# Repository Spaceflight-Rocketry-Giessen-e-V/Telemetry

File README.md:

# ASCENT Rocket Telemetry System

|</p> | </p></p>|
|---|---|
|<p align="center">[The Onboard System](/onboard/)</p>|<p align="center">[The Groundstation System](/groundstation/)</p>|

---

## Overview

The ASCENT telemetry system is a part of the ASCENT flight computer, which is being developed by the student rocketry club [Spaceflight Rocketry Gießen e.V.](https://sprog-ev.de/en/) for the PIPE and ARCHER experimental rockets.
This dual-frequency 169/869-MHz telemetry system based on Radiocrafts RC232 radio modules allows bidirectional data exchange between rockets and groundstations with a range of more than 10 km.
The design can easily be adapted for uses outside of rocketry like Smart Home or RC.

## Basic Functionality

- Receiving flight and telemetry data from the rocket
- Sending radio commands to the rocket
- Displaying live data on a serial monitor or an UI

## Actual Performance

In January 2026, we performed our first long range test over a distance of 2 km. Despite poor weather conditions and objects inside the first Fresnel zone, the received signal strength was on par with the theoretical maximum without any unaccounted losses. This test ruled out major design flaws and was confirmed by additional medium range tests.

In April 2026, the system was successfully tested on the PIPE 2 rocket to an altitude of 350 m and experienced no link issues during the whole flight.

---

## Repository Contents

This repository contains all files necessary to reproduce the telemetry system, including hardware, firmware, software, and documentation.

### 1. Electronics Hardware

The telemetry system utilizes separate [onboard](/onboard/pcb/) and [groundstation](/groundstation/pcb/) electronics.
The groundstation uses a modular approach with a [motherboard](/groundstation/pcb/Motherboard/) to which up to four [daughterboards](/groundstation/pcb/Daughterboard/) with radio modules can be connected.

The repository includes for each system the KiCad design files including custom component schematic, footprint, and 3D model libraries, the PDF schematic, the Gerber production files, the bill of material (BOM) and an interactive BOM (iBOM). 
Renderings, images, and 3D models of the electronics are also included.

The [onboard mounting structure](/onboard/mounting%20structure/), the [motherboard and daughterboard casings](/groundstation/casing/) are included separately.

### 2. Antenna Hardware

So far, this repository includes the [design files](/groundstation/antenna/helical/) and [assembly instructions](/docs/helical_antenna_assembly_manual.md) for our helical 869 MHz groundstation antenna.

We also do our own FDTD-simulations which can be found [here](groundstation/antenna/helical/Simulation/Helical_Antenna.m).

Currently, we are developing an 869 MHz QFH antenna.

### 3. Firmware

- [Onboard Firmware](/onboard/firmware/)
- [Groundstation Firmware](/groundstation/firmware/) 
- [Radiocrafts RC17xHP-RC232 Library](/libraries/Radiocrafts_RC17xxHP_RC232/)
- [Dynamic Package Codec (Encoding/Decoding) Library](/libraries/DynamicPacketCodec/)
- [Firmware API Reference](https://spaceflight-rocketry-giessen-e-v.github.io/Telemetry/)

### 4. Groundstation UI Software

[Python-based software](/groundstation/gui/) to display live telemetry data on a modern, minimalistic interface with the ability to store flight data and send radio commands. 

Widgets include a GNSS map view, a height plot over time, an acceleration plot over time, a battery voltage indicator with visual warnings, a connection quality indicator with visual warnings, and a status event indicator.

### 5. Documentation

- [Design Overview](/docs/design_overview.md)
- [User Manual](/docs/user_manual.md) and [Operations Cheatsheet](/docs/operations_cheatsheet.md)
- Documentation of the [Packet Structure](/docs/packet_structure.md) and the [Linkbudget Calculation](/docs/linkbudget.ipynb)
- [And more...](/docs/)

---

## Legal Notice

Please note that radio systems may be subject to local regulations. Ensure that any testing or deployment of these systems complies with national and regional laws regarding RF transmission. Spaceflight Rocketry Giessen e.V. and the individual project contributors are not responsible for misuse or regulatory violations.  

## License

This source describes Open Hardware and is licensed under the CERN-OHL-S v2.<br>
You may redistribute and modify this source and make products using it under the terms of the [CERN-OHL-S v2 or any later version](LICENSE).<br>
This source is distributed without any express or implied warranty, including of merchantability, satifactory quality and fitness for a particular purpose. Please see the CERN-OHL-S v2 for applicable conditions.<br>
Source location: https://github.com/Spaceflight-Rocketry-Giessen-e-V/Telemetry<br>
As per CERN-OHL-S v2 section 4, should you produce hardware based on this source, you must where practicable maintain the Source Location in its documentation or license information.<br><br>
Copyright 2026 Spaceflight Rocketry Giessen e.V. \<elektronik@sprog-ev.de\>

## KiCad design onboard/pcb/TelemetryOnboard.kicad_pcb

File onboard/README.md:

# The Onboard System

- [Electronics Hardware](/onboard/pcb/)
    - [KiCad Design Files](/onboard/pcb/)
    - [PDF Schematic](/onboard/pcb/TelemetryOnboard_Schematic.pdf)
    - [Interactive Schematic / iBOM](/onboard/pcb/TelemetryOnboard_iBOM.html)
    - [BOM](/onboard/pcb/TelemetryOnboard_BOM.csv)
    - [Gerber Files](/onboard/pcb/Production%20Files/)
    - [PCB 3D Model](/onboard/pcb/TelemetryOnboard.step)
    - [PCB Images](/onboard/pcb/images/)
- [Mounting Structure](/onboard/mounting%20structure/)
- [Firmware](/onboard/firmware/)
- [869 MHz QFH Antenna](/onboard/antenna/) (not yet available)

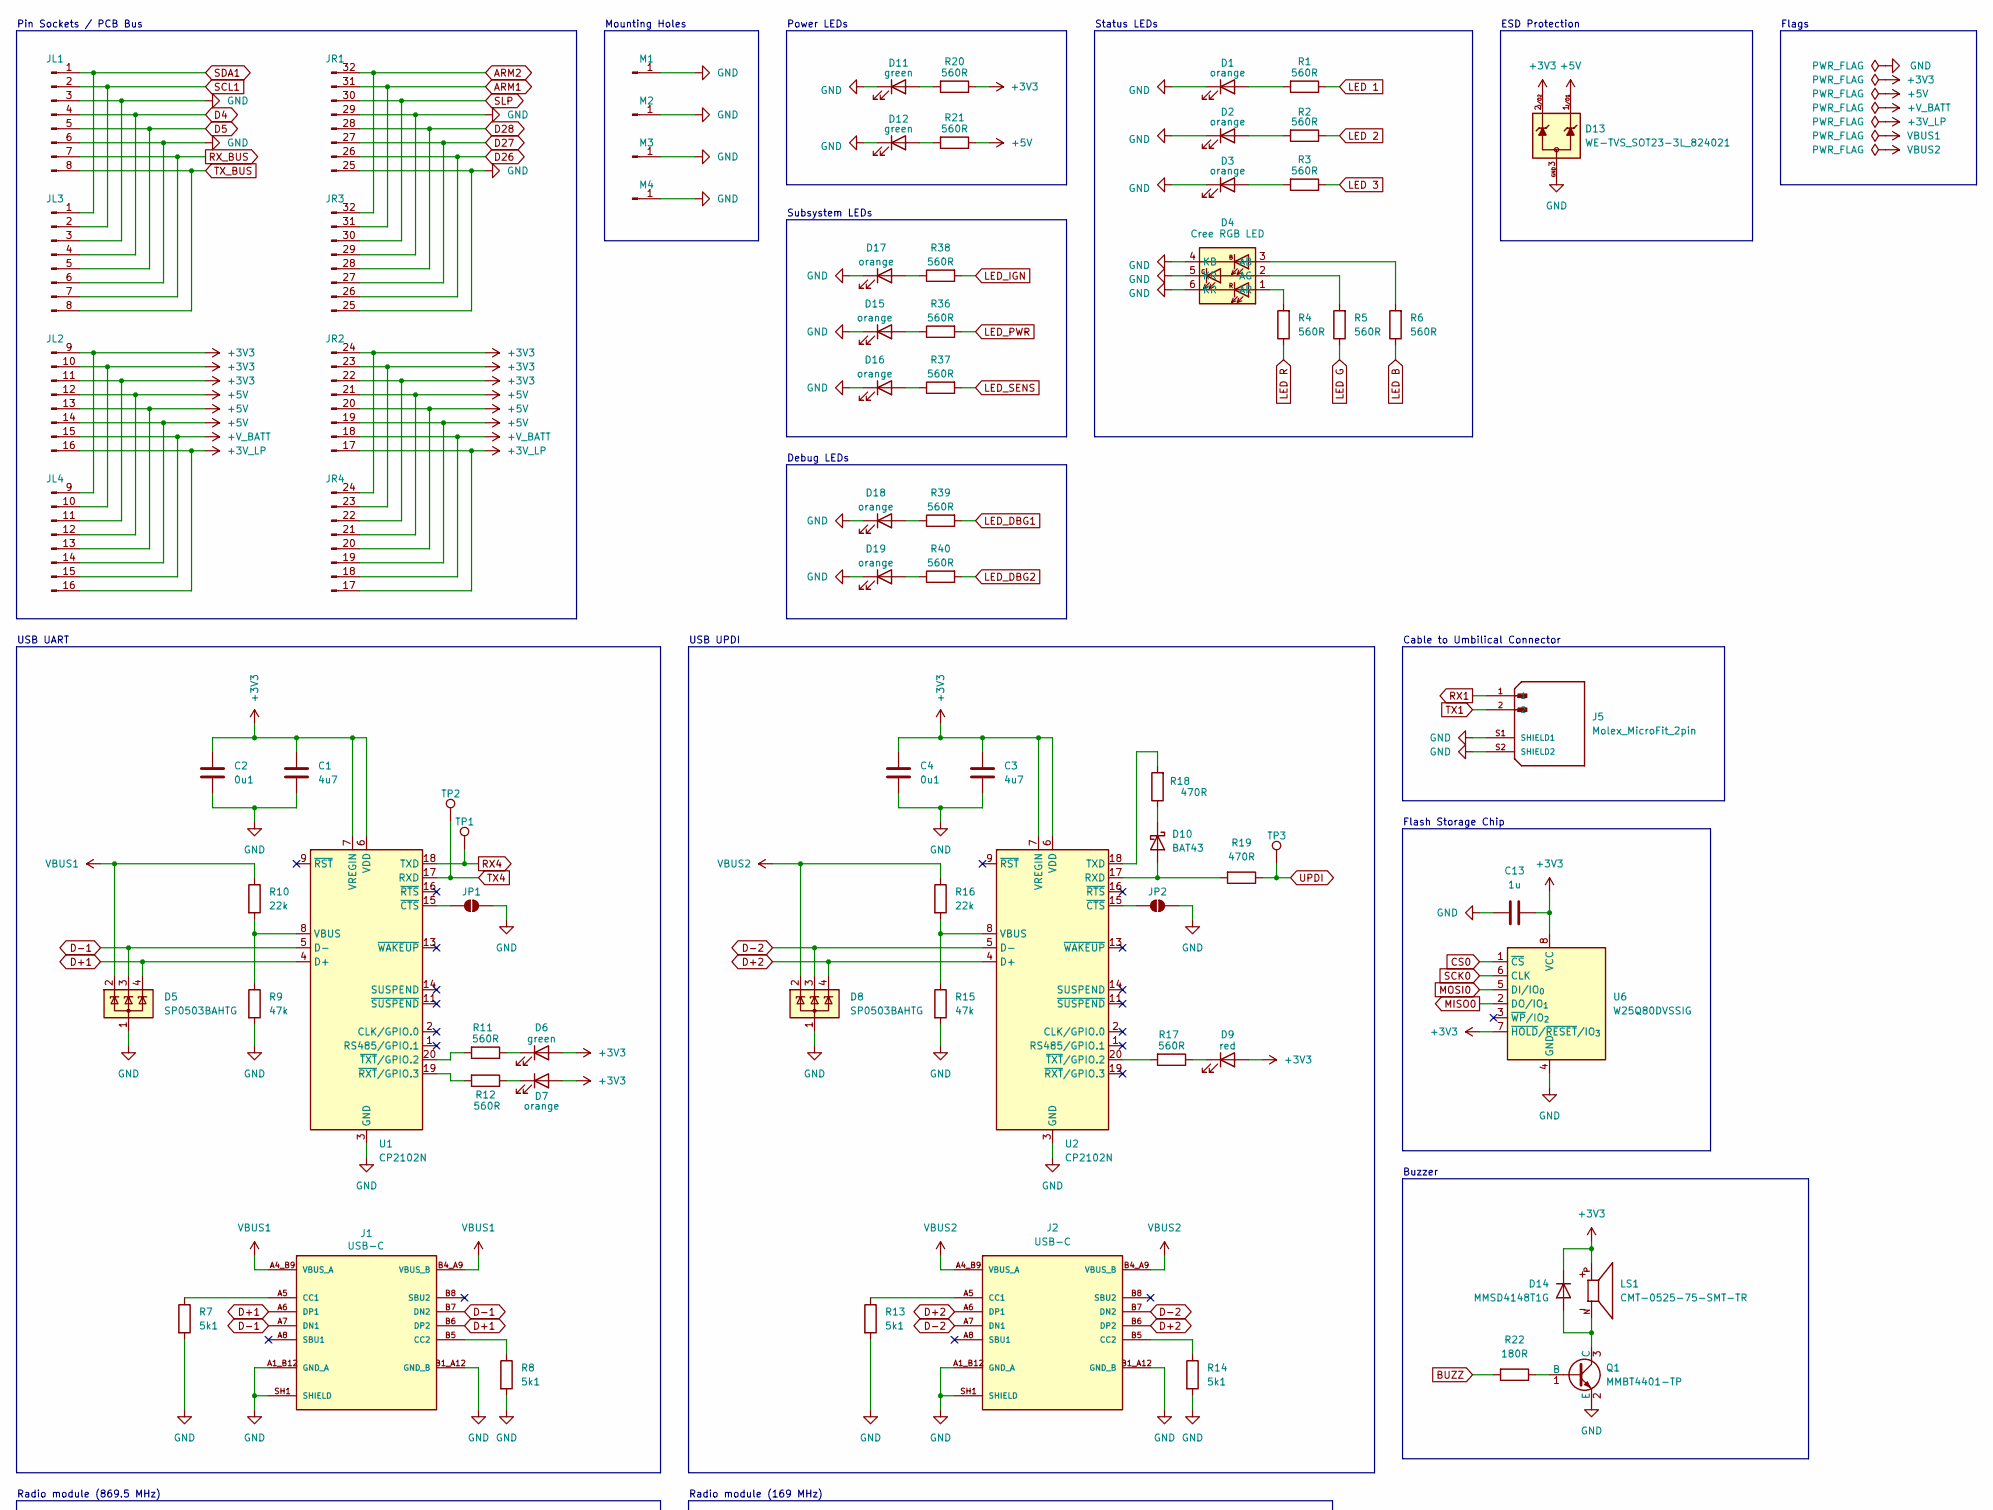
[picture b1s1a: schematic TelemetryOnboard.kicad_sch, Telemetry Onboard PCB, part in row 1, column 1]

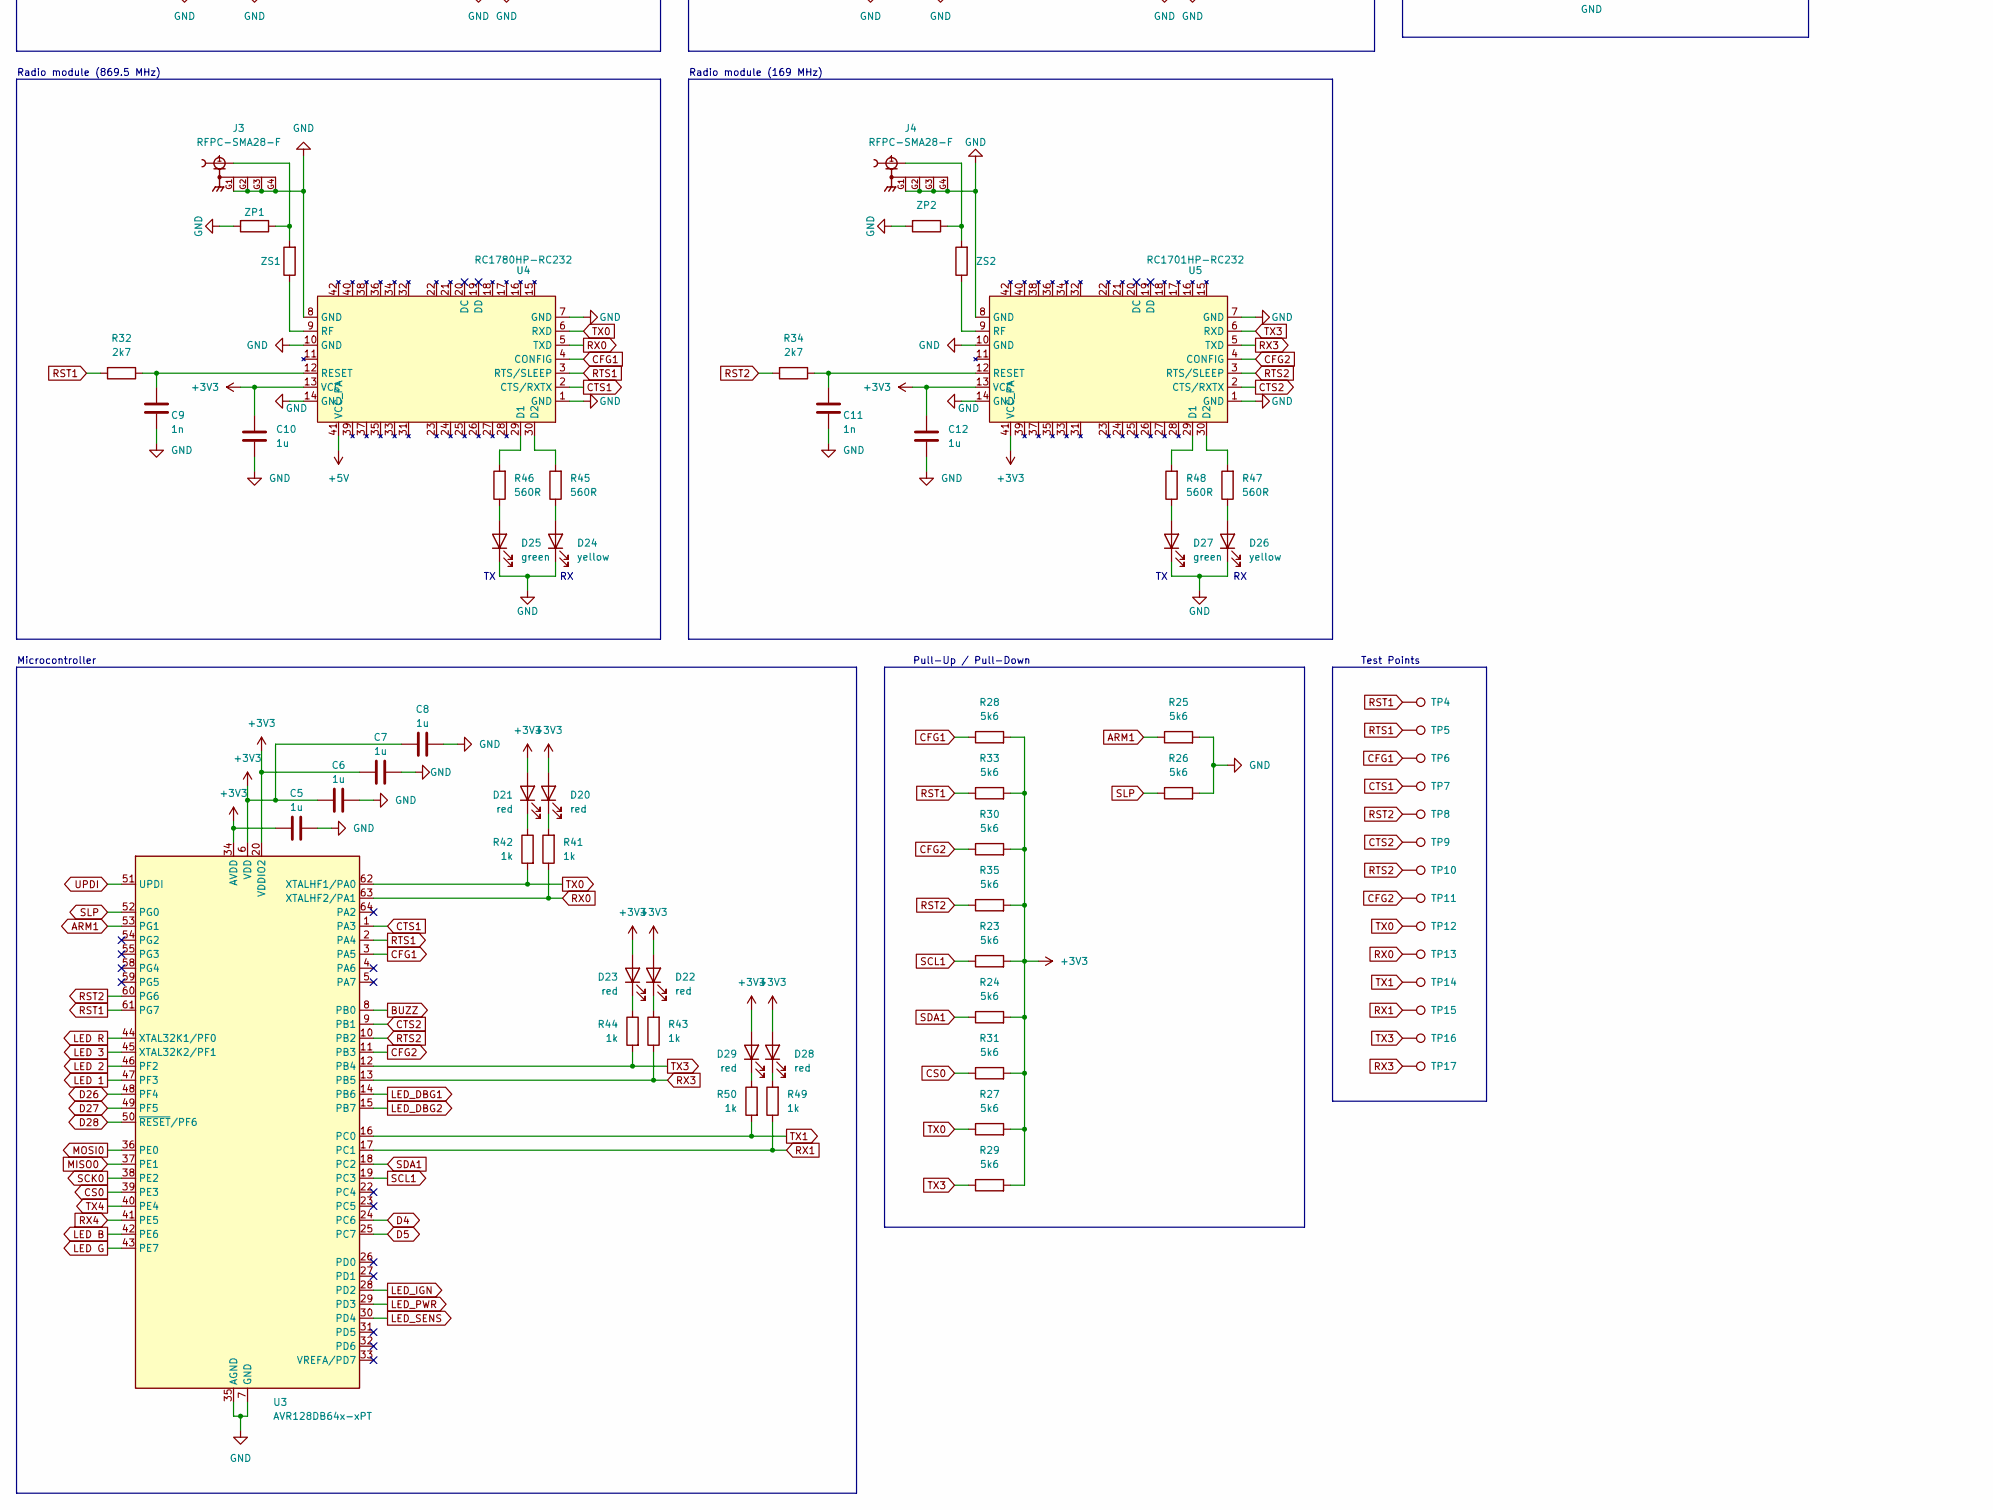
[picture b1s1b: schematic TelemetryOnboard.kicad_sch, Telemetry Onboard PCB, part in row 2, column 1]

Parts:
C1, C3: 4u7; C_0805_2012Metric_Pad1.18x1.45mm_HandSolder
C2, C4: 0u1; C_0805_2012Metric_Pad1.18x1.45mm_HandSolder
C5, C6, C7, C8, C10, C12, C13: 1u; C_0805_2012Metric_Pad1.18x1.45mm_HandSolder
C9, C11: 1n; C_0805_2012Metric_Pad1.18x1.45mm_HandSolder
D1, D2, D3, D7, D15, D16, D17, D18, D19: orange; LED_0805_2012Metric_Pad1.15x1.40mm_HandSolder
D4: Cree RGB LED; Cree_PLCC6_RGB
D5, D8: SP0503BAHTG; SOT-143
D6, D11, D12, D25, D27: green; LED_0805_2012Metric_Pad1.15x1.40mm_HandSolder
D9, D20, D21, D22, D23, D28, D29: red; LED_0805_2012Metric_Pad1.15x1.40mm_HandSolder
D10: BAT43; D_SOD-123
D13: WE-TVS_SOT23-3L_824021; SOT-23-3
D14: MMSD4148T1G; D_SOD-123
D24, D26: yellow; LED_0805_2012Metric_Pad1.15x1.40mm_HandSolder
J1, J2: USB-C; GTC_USB4216_SMD; PARTREV A; DigiKey_Part_Number 2073-USB4215-03-ACT-ND
J3, J4: RFPC-SMA28-F; SMA_Amphenol_901-144_Vertical; PARTREV 1.0; DigiKey_Part_Number 2073-RFPC-SMA28-F-ND
J5: Molex_MicroFit_2pin; Molex_MicroFit-2pos; PARTREV F3; DigiKey_Part_Number WM1870-ND
JL1: Stackable Socket 1x8; JL1
JL2: Stackable Socket 1x8; JL2
JL3: Stackable Socket 1x8; JL3
JL4: Stackable Socket 1x8; JL4
JP1, JP2: SolderJumper_2_Open; Custom_SolderJumper
JR1: Stackable Socket 1x8; JR1
JR2: Stackable Socket 1x8; JR2
JR3: Stackable Socket 1x8; JR3
JR4: Stackable Socket 1x8; JR4
LS1: CMT-0525-75-SMT-TR; SameSky_CMT-0525-75-SMT_Buzzer; PARTREV 1.0
M1, M2, M3, M4: M4 Mounting Hole; Custom_M4Hole
Q1: MMBT4401-TP; SOT-23
R1, R2, R3, R4, R5, R6, R11, R12, R17, R20, R21, R36, R37, R38, R39, R40, R45, R46, R47, R48: 560R; R_0805_2012Metric_Pad1.20x1.40mm_HandSolder
R7, R8, R13, R14: 5k1; R_0805_2012Metric_Pad1.20x1.40mm_HandSolder
R9, R15: 47k; R_0805_2012Metric_Pad1.20x1.40mm_HandSolder
R10, R16: 22k; R_0805_2012Metric_Pad1.20x1.40mm_HandSolder
R18, R19: 470R; R_0805_2012Metric_Pad1.20x1.40mm_HandSolder
R22: 180R; R_0805_2012Metric_Pad1.20x1.40mm_HandSolder
R23, R24, R25, R26, R27, R28, R29, R30, R31, R33, R35: 5k6; R_0805_2012Metric_Pad1.20x1.40mm_HandSolder
R32, R34: 2k7; R_0805_2012Metric_Pad1.20x1.40mm_HandSolder
R41, R42, R43, R44, R49, R50: 1k; R_0805_2012Metric_Pad1.20x1.40mm_HandSolder
TP1, TP2, TP3, TP4, TP5, TP6, TP7, TP8, TP9, TP10, TP11, TP12, TP13, TP14, TP15, TP16, TP17: TestPoint; Custom_SolderJumper
U1, U2: CP2102N; SiLabs_CP2102N_QFN20.step
U3: AVR128DB64x-xPT; TQFP-64_10x10mm_P0.5mm
U4: RC1780HP-RC232; Radiocrafts_RC17xxHP-RC232
U5: RC1701HP-RC232; Radiocrafts_RC17xxHP-RC232
U6: W25Q80DVSSIG; SOIC-8_5.3x5.3mm_P1.27mm
ZP1, ZP2: R_0805_2012Metric_Pad1.20x1.40mm_HandSolder
ZS1, ZS2: R_0805_2012Metric_Pad1.20x1.40mm_HandSolder

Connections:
+3V3: C1.1, C2.1, C3.1, C4.1, C5.1, C6.1, C7.2, C8.2, C10.1, C12.1, C13.2, D6.2 (A), D7.2 (A), D9.2 (A), D13.2 (K), D14.1 (K), D20.2 (A), D21.2 (A), D22.2 (A), D23.2 (A), D28.2 (A), D29.2 (A), JL2.9 (Pin_1), JL2.10 (Pin_2), JL2.11 (Pin_3), JL4.9 (Pin_1), JL4.10 (Pin_2), JL4.11 (Pin_3), JR2.22 (26), JR2.23 (Pin_2), JR2.24 (Pin_1), JR4.22 (26), JR4.23 (Pin_2), JR4.24 (Pin_1), LS1.P, R20.1, R23.2, R24.2, R27.2, R28.2, R29.2, R30.2, R31.2, R33.2, R35.2, U1.6 (VDD), U1.7 (VREGIN), U2.6 (VDD), U2.7 (VREGIN), U3.6 (VDD), U3.20 (VDDIO2), U3.34 (AVDD), U3.56 (VDD), U4.13 (VCC), U5.13 (VCC), U5.41 (VCC_PA), U6.7 (~HOLD/~RESET/IO_{3}), U6.8 (VCC)
+3V_LP: JL2.16 (Pin_8), JL4.16 (Pin_8), JR2.17 (Pin_8), JR4.17 (Pin_8)
+5V: D13.1 (K), JL2.12 (Pin_4), JL2.13 (Pin_5), JL2.14 (Pin_6), JL4.12 (Pin_4), JL4.13 (Pin_5), JL4.14 (Pin_6), JR2.19 (Pin_6), JR2.20 (Pin_5), JR2.21 (Pin_4), JR4.19 (Pin_6), JR4.20 (Pin_5), JR4.21 (Pin_4), R21.1, U4.41 (VCC_PA)
+V_BATT: JL2.15 (Pin_7), JL4.15 (Pin_7), JR2.18 (Pin_7), JR4.18 (Pin_7)
ARM1: JR1.31 (Pin_2), JR3.31 (Pin_2), R25.1, U3.53 (PG1)
ARM2: JR1.32 (Pin_1), JR3.32 (Pin_1)
BUZZ: R22.2, U3.8 (PB0)
CFG1: R28.1, TP6.1 (1_1), U3.3 (PA5), U4.4 (CONFIG)
CFG2: R30.1, TP11.1 (1_1), U3.11 (PB3), U5.4 (CONFIG)
CS0: R31.1, U3.39 (PE3), U6.1 (~CS)
CTS1: TP7.1 (1_1), U3.1 (PA3), U4.2 (CTS/RXTX)
CTS2: TP9.1 (1_1), U3.9 (PB1), U5.2 (CTS/RXTX)
D4: JL1.4, JL3.4, U3.24 (PC6)
D5: JL1.5, JL3.5, U3.25 (PC7)
D26: JR1.26 (Pin_7), JR3.26 (Pin_7), U3.48 (PF4)
D27: JR1.27 (Pin_6), JR3.27 (Pin_6), U3.49 (PF5)
D28: JR1.28 (Pin_5), JR3.28 (Pin_5), U3.50 (~RESET/PF6)
D+1: D5.4 (K), J1.A6 (DP1), J1.B6 (DP2), U1.4 (D+)
D+2: D8.4 (K), J2.A6 (DP1), J2.B6 (DP2), U2.4 (D+)
D-1: D5.3 (K), J1.A7 (DN1), J1.B7 (DN2), U1.5 (D-)
D-2: D8.3 (K), J2.A7 (DN1), J2.B7 (DN2), U2.5 (D-)
GND: C1.2, C2.2, C3.2, C4.2, C5.2, C6.2, C7.1, C8.1, C9.2, C10.2, C11.2, C12.2, C13.1, D1.1 (K), D2.1 (K), D3.1 (K), D4.4 (KB), D4.5 (KG), D4.6 (KR), D5.1 (A), D8.1 (A), D11.1 (K), D12.1 (K), D13.3 (A), D15.1 (K), D16.1 (K), D17.1 (K), D18.1 (K), D19.1 (K), D24.1 (K), D25.1 (K), D26.1 (K), D27.1 (K), J1.A1_B12 (GND_A), J1.B1_A12 (GND_B), J1.SH1 (SHIELD), J1.SH2 (SHIELD), J1.SH3 (SHIELD), J1.SH4 (SHIELD), J2.A1_B12 (GND_A), J2.B1_A12 (GND_B), J2.SH1 (SHIELD), J2.SH2 (SHIELD), J2.SH3 (SHIELD), J2.SH4 (SHIELD), J3.2 (Ext), J3.G1, J3.G2, J3.G3, J3.G4, J4.2 (Ext), J4.G1, J4.G2, J4.G3, J4.G4, J5.S1 (SHIELD), J5.S2 (SHIELD), JL1.3, JL1.6, JL3.3, JL3.6, JP1.2 (B), JP2.2 (B), JR1.25 (Pin_8), JR1.29 (Pin_4), JR3.25 (Pin_8), JR3.29 (Pin_4), M1.1 (Pin_1_1), M2.1 (Pin_1_1), M3.1 (Pin_1_1), M4.1 (Pin_1_1), Q1.2 (E), R7.2, R8.2, R9.2, R13.2, R14.2, R15.2, R25.2, R26.2, U1.3 (GND), U1.12 (GND), U1.21 (GND), U2.3 (GND), U2.12 (GND), U2.21 (GND), U3.7 (GND), U3.21 (GND), U3.35 (AGND), U3.57 (GND), U4.1 (GND), U4.7 (GND), U4.8 (GND), U4.10 (GND), U4.14 (GND), U5.1 (GND), U5.7 (GND), U5.8 (GND), U5.10 (GND), U5.14 (GND), U6.4 (GND), ZP1.2, ZP2.2
LED 1: R1.1, U3.47 (PF3)
LED 2: R2.1, U3.46 (PF2)
LED 3: R3.1, U3.45 (XTAL32K2/PF1)
LED B: R6.1, U3.42 (PE6)
LED G: R5.1, U3.43 (PE7)
LED R: R4.1, U3.44 (XTAL32K1/PF0)
LED_DBG1: R39.2, U3.14 (PB6)
LED_DBG2: R40.2, U3.15 (PB7)
LED_IGN: R38.2, U3.28 (PD2)
LED_PWR: R36.2, U3.29 (PD3)
LED_SENS: R37.2, U3.30 (PD4)
MISO0: U3.37 (PE1), U6.2 (DO/IO_{1})
MOSI0: U3.36 (PE0), U6.5 (DI/IO_{0})
unnamed: D1.2 (A), R1.2
unnamed: D2.2 (A), R2.2
unnamed: D3.2 (A), R3.2
unnamed: D4.3 (AB), R6.2
unnamed: D4.2 (AG), R5.2
unnamed: D4.1 (AR), R4.2
unnamed: D6.1 (K), R11.1
unnamed: D7.1 (K), R12.1
unnamed: D9.1 (K), R17.1
unnamed: D10.2 (A), R19.2, U2.17 (RXD)
unnamed: D10.1 (K), R18.1
unnamed: D11.2 (A), R20.2
unnamed: D12.2 (A), R21.2
unnamed: D14.2 (A), LS1.N, Q1.3 (C)
unnamed: D15.2 (A), R36.1
unnamed: D16.2 (A), R37.1
unnamed: D17.2 (A), R38.1
unnamed: D18.2 (A), R39.1
unnamed: D19.2 (A), R40.1
unnamed: D20.1 (K), R41.2
unnamed: D21.1 (K), R42.1
unnamed: D22.1 (K), R43.2
unnamed: D23.1 (K), R44.1
unnamed: D24.2 (A), R45.1
unnamed: D25.2 (A), R46.1
unnamed: D26.2 (A), R47.1
unnamed: D27.2 (A), R48.1
unnamed: D28.1 (K), R49.2
unnamed: D29.1 (K), R50.1
unnamed: J1.A5 (CC1), R7.1
unnamed: J1.B5 (CC2), R8.1
unnamed: J2.A5 (CC1), R13.1
unnamed: J2.B5 (CC2), R14.1
unnamed: J3.1 (In), ZP1.1, ZS1.2
unnamed: J4.1 (In), ZP2.1, ZS2.2
unnamed: JP1.1 (A), U1.15 (~CTS)
unnamed: JP2.1 (A), U2.15 (~CTS)
unnamed: Q1.1 (B), R22.1
unnamed: R9.1, R10.2, U1.8 (VBUS)
unnamed: R12.2, U1.19 (~RXT/GPIO.3)
unnamed: R11.2, U1.20 (~TXT/GPIO.2)
unnamed: R18.2, U2.18 (TXD)
unnamed: R15.1, R16.2, U2.8 (VBUS)
unnamed: R17.2, U2.20 (~TXT/GPIO.2)
unnamed: R46.2, U4.29 (D1)
unnamed: R45.2, U4.30 (D2)
unnamed: C9.1, R32.1, U4.12 (RESET)
unnamed: U4.9 (RF), ZS1.1
unnamed: R48.2, U5.29 (D1)
unnamed: R47.2, U5.30 (D2)
unnamed: C11.1, R34.1, U5.12 (RESET)
unnamed: U5.9 (RF), ZS2.1
RST1: R32.2, R33.1, TP4.1 (1_1), U3.61 (PG7)
RST2: R34.2, R35.1, TP8.1 (1_1), U3.60 (PG6)
RTS1: TP5.1 (1_1), U3.2 (PA4), U4.3 (RTS/SLEEP)
RTS2: TP10.1 (1_1), U3.10 (PB2), U5.3 (RTS/SLEEP)
RX0: R41.1, TP13.1 (1_1), U3.63 (XTALHF2/PA1), U4.5 (TXD)
RX1: J5.1, R49.1, TP15.1 (1_1), U3.17 (PC1)
RX3: R43.1, TP17.1 (1_1), U3.13 (PB5), U5.5 (TXD)
RX4: TP1.1 (1_1), U1.18 (TXD), U3.41 (PE5)
RX_BUS: JL1.7, JL3.7
SCK0: U3.38 (PE2), U6.6 (CLK)
SCL1: JL1.2, JL3.2, R23.1, U3.19 (PC3)
SDA1: JL1.1, JL3.1, R24.1, U3.18 (PC2)
SLP: JR1.30 (26), JR3.30 (26), R26.1, U3.52 (PG0)
TX0: R27.1, R42.2, TP12.1 (1_1), U3.62 (XTALHF1/PA0), U4.6 (RXD)
TX1: J5.2, R50.2, TP14.1 (1_1), U3.16 (PC0)
TX3: R29.1, R44.2, TP16.1 (1_1), U3.12 (PB4), U5.6 (RXD)
TX4: TP2.1 (1_1), U1.17 (RXD), U3.40 (PE4)
TX_BUS: JL1.8, JL3.8
UPDI: R19.1, TP3.1 (1_1), U3.51 (UPDI)
VBUS1: D5.2 (K), J1.A4_B9 (VBUS_A), J1.B4_A9 (VBUS_B), R10.1
VBUS2: D8.2 (K), J2.A4_B9 (VBUS_A), J2.B4_A9 (VBUS_B), R16.1

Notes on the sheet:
Subsystem LEDs
Pull-Up / Pull-Down
Pin Sockets / PCB Bus
Flash Storage Chip
Microcontroller
Radio module (169 MHz)
Flags
USB UPDI
Test Points
Buzzer
USB UART
Status LEDs
Debug LEDs
Mounting Holes
Power LEDs
ESD Protection
Radio module (869.5 MHz)
Cable to Umbilical Connector

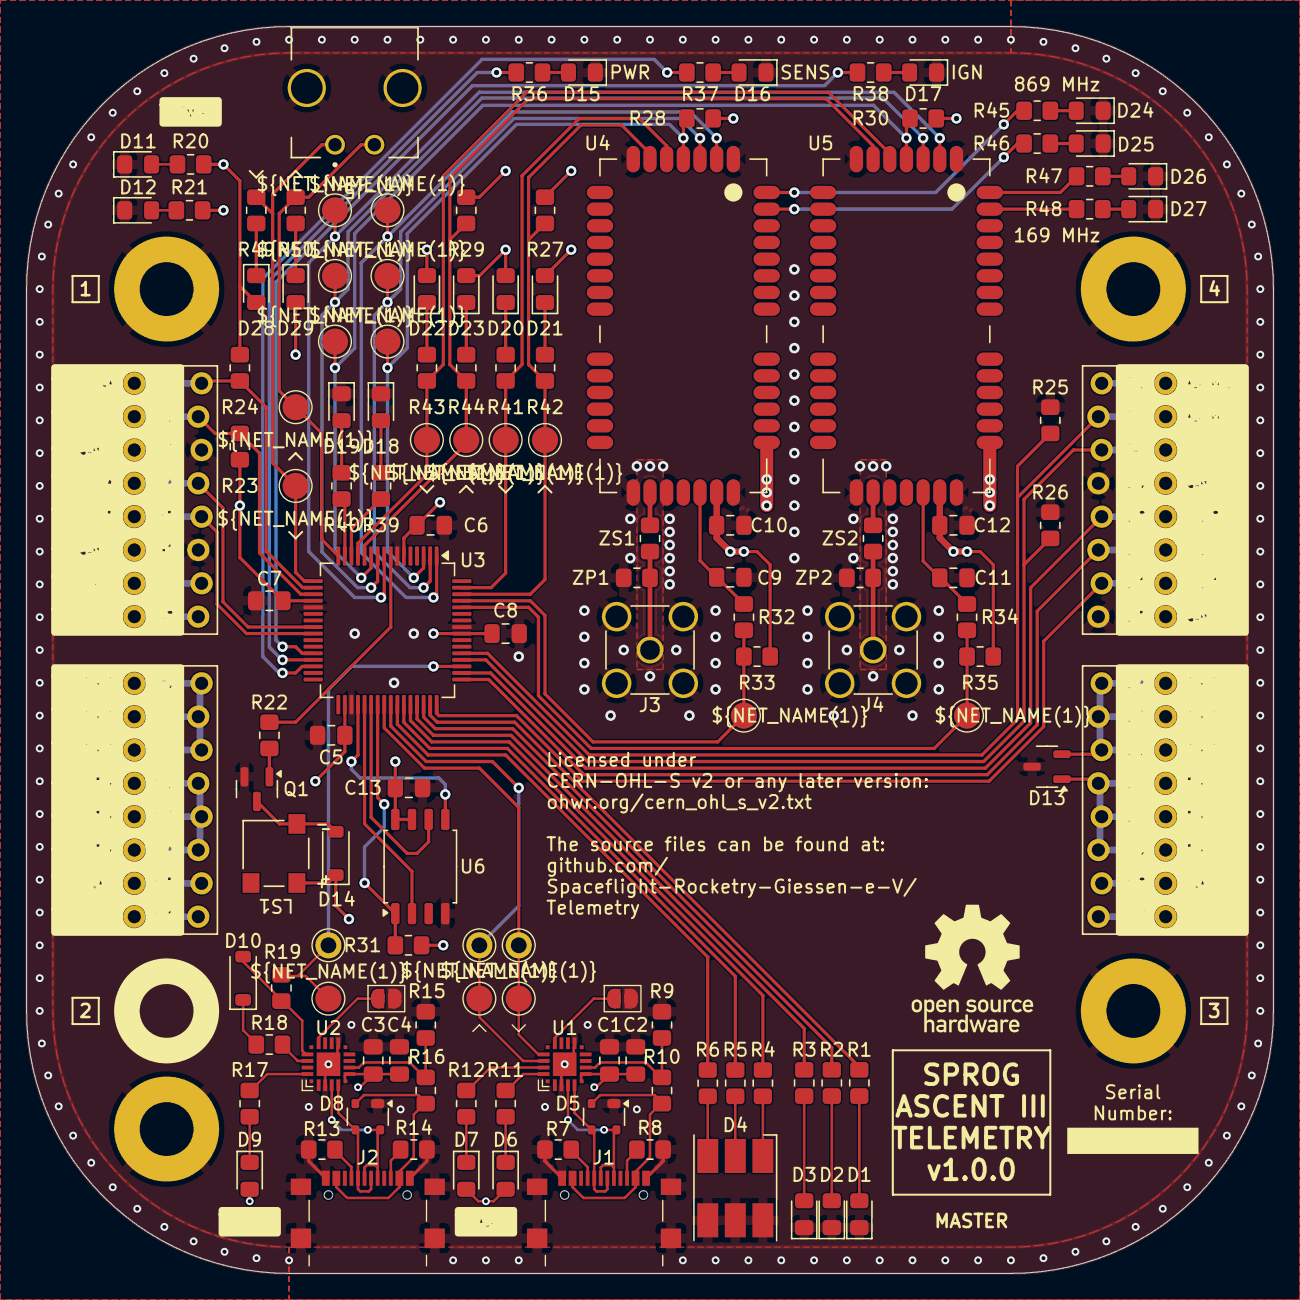
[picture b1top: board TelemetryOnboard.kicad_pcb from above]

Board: 4 copper layers, 95.0 x 95.0 mm, 140 parts (0 on the bottom side), 108 nets.

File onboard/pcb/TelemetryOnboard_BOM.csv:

"Reference","Qty","Value","Footprint","DNP","Purchase-URL"
"C1,C3","2","4u7","Capacitor_SMD:C_0805_2012Metric_Pad1.18x1.45mm_HandSolder","","https://www.digikey.de/de/products/detail/samsung-electro-me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"
"C2,C4","2","0u1","Capacitor_SMD:C_0805_2012Metric_Pad1.18x1.45mm_HandSolder","","https://www.digikey.de/de/products/detail/samsung-electro-me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"
"C5,C6,C7,C8,C10,C12,C13","7","1u","Capacitor_SMD:C_0805_2012Metric_Pad1.18x1.45mm_HandSolder","","https://www.digikey.de/de/products/detail/samsung-electro-me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"
"C9,C11","2","1n","Capacitor_SMD:C_0805_2012Metric_Pad1.18x1.45mm_HandSolder","","https://www.digikey.de/de/products/detail/samsung-electro-me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"
"D1,D2,D3,D7,D15,D16,D17,D18,D19","9","orange","LED_SMD:LED_0805_2012Metric_Pad1.15x1.40mm_HandSolder","","https://www.digikey.de/de/products/detail/liteon/LTST-C170KF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"
"D4","1","Cree RGB LED","Footprints:Cree RGB LED","","https://www.digikey.de/de/products/detail/cree-led/CLP6C-FKB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"
"D5,D8","2","SP0503BAHTG","Package_TO_SOT_SMD:SOT-143","","https://www.digikey.de/de/products/detail/littelfuse-inc/SP0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"
"D6,D11,D12,D25,D27","5","green","LED_SMD:LED_0805_2012Metric_Pad1.15x1.40mm_HandSolder","","https://www.digikey.de/de/products/detail/liteon/LTST-C171KG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"
"D9,D20,D21,D22,D23,D28,D29","7","red","LED_SMD:LED_0805_2012Metric_Pad1.15x1.40mm_HandSolder","","https://www.digikey.de/de/products/detail/liteon/LTST-C171KR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"
"D10","1","BAT43","Diode_SMD:D_SOD-123","","https://www.digikey.de/de/products/detail/mcc-micro-commerci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"
"D13","1","WE-TVS_SOT23-3L_824021","Package_TO_SOT_SMD:SOT-23-3","","https://www.digikey.de/de/products/detail/w%C3%BCrth-elektro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"
"D14","1","MMSD4148T1G","Diode_SMD:D_SOD-123","","https://www.digikey.de/de/products/detail/onsemi/MMSD4148T1G/919705"
"D24,D26","2","yellow","LED_SMD:LED_0805_2012Metric_Pad1.15x1.40mm_HandSolder","","https://www.digikey.de/de/products/detail/liteon/LTST-C170KS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"
"J1,J2","2","USB-C","Footprints:GCT_USB4216-03-A_REVA","","https://www.digikey.de/de/products/detail/gct/USB4216-03-A/26598207"
"J3,J4","2","RFPC-SMA28-F","Footprints:RFPC-SMA28-F","","https://www.digikey.de/de/products/detail/gct/RFPC-SMA28-F/2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"
"J5","1","Molex_MicroFit_2pin","Footprints:Molex_MicroFit_2pin","","https://www.digikey.de/de/products/detail/molex/0436500203/268999"
"JL1,JL2,JL3,JL4","4","Stackable Socket 1x8","Footprints:JL1,Footprints:JL2,Footprints:JL3,Footprints:JL4","","https://www.digikey.de/de/products/detail/samtec-inc/ESQ-108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,~"
"JR1,JR2,JR3,JR4","4","Stackable Socket 1x8","Footprints:JR1,Footprints:JR2,Footprints:JR3,Footprints:JR4","","https://www.digikey.de/de/products/detail/samtec-inc/ESQ-108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,~"
"LS1","1","CMT-0525-75-SMT-TR","Footprints:Buzzer XDCR_CMT-0525-75-SMT-TR","","https://www.digikey.de/de/products/detail/same-sky-formerly-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"
"M1,M2,M3,M4","4","M4 Mounting Hole","Footprints:M4 Mounting Hole","","~"
"Q1","1","MMBT4401-TP","Package_TO_SOT_SMD:SOT-23","","https://www.digikey.de/de/products/detail/mcc-micro-commerci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"
"R1,R2,R3,R4,R5,R6,R11,R12,R17,R20,R21,R36,R37,R38,R39,R40,R45,R46,R47,R48","20","560R","Resistor_SMD:R_0805_2012Metric_Pad1.20x1.40mm_HandSolder","","https://www.digikey.de/de/products/detail/stackpole-electron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"
"R7,R8,R13,R14","4","5k1","Resistor_SMD:R_0805_2012Metric_Pad1.20x1.40mm_HandSolder","","https://www.digikey.de/de/products/detail/stackpole-electron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"
"R9,R15","2","47k","Resistor_SMD:R_0805_2012Metric_Pad1.20x1.40mm_HandSolder","","https://www.digikey.de/de/products/detail/stackpole-electron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"
"R10,R16","2","22k","Resistor_SMD:R_0805_2012Metric_Pad1.20x1.40mm_HandSolder","","https://www.digikey.de/de/products/detail/stackpole-electron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"
"R18,R19","2","470R","Resistor_SMD:R_0805_2012Metric_Pad1.20x1.40mm_HandSolder","","https://www.digikey.de/de/products/detail/stackpole-electron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"
"R22","1","180R","Resistor_SMD:R_0805_2012Metric_Pad1.20x1.40mm_HandSolder","","https://www.digikey.de/de/products/detail/stackpole-electron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"
"R23,R24,R25,R26,R27,R28,R29,R30,R31,R33,R35","11","5k6","Resistor_SMD:R_0805_2012Metric_Pad1.20x1.40mm_HandSolder","","https://www.digikey.de/de/products/detail/stackpole-electron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"
"R32,R34","2","2k7","Resistor_SMD:R_0805_2012Metric_Pad1.20x1.40mm_HandSolder","","https://www.digikey.de/de/products/detail/stackpole-electron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"
"R41,R42,R43,R44,R49,R50","6","1k","Resistor_SMD:R_0805_2012Metric_Pad1.20x1.40mm_HandSolder","","https://www.digikey.de/de/products/detail/stackpole-electron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"
"TP1,TP2,TP3,TP4,TP5,TP6,TP7,TP8,TP9,TP10,TP11,TP12,TP13,TP14,TP15,TP16,TP17","17","TestPoint","Footprints:Test Point","","~"
"U1,U2","2","CP2102N","Footprints:QFN20_CP2102N_SIL","","https://www.digikey.de/de/products/detail/silicon-labs/CP210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"
"U3","1","AVR128DB64x-xPT","Package_QFP:TQFP-64_10x10mm_P0.5mm","","https://www.digikey.de/de/products/detail/microchip-technolo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"
"U4","1","RC1780HP-RC232","Footprints:Radiocrafts RC1780HP-RC232","","https://www.digikey.de/de/products/detail/radiocrafts-as/RC1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"
"U5","1","RC1701HP-RC232","Footprints:Radiocrafts RC1780HP-RC232","","https://www.digikey.de/de/products/detail/radiocrafts-as/RC1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"
"U6","1","W25Q80DVSSIG","Package_SO:SOIC-8_5.3x5.3mm_P1.27mm","","https://www.digikey.de/de/products/detail/winbond-electronic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"
"ZP1,ZP2","2","~","Resistor_SMD:R_0805_2012Metric_Pad1.20x1.40mm_HandSolder","","~"
"ZS1,ZS2","2","~","Resistor_SMD:R_0805_2012Metric_Pad1.20x1.40mm_HandSolder","","~"

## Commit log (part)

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2025-12-11 add parachute deployment capability and parity check
    fixes #10
2025-12-11 add more documentation for handling the groundstation
2025-12-14 change main deployment behaviour
2025-12-27 fix link typo
2025-12-27 fix link typo and add documentation
2025-12-28 add documentation to the RC1780HP library
    fixes #9
2025-12-28 Add comments on RC1780 library
2026-01-04 Meerkat: Fix images
2026-01-08 improve documentation
    added documentation text and images and informations about versioning
2026-01-14 fix firmware bug
2026-01-23 update and move firmware libraries
    redo rc17xxhp lib and move both libs to a major folder
2026-01-26 fix small typo
2026-01-26 move image positions
2026-02-02 update gitignore
2026-02-05 update platine
2026-02-06 Led resistor from 270 to 560+
2026-02-11 change usb connector and add tvs diode
2026-02-11 add groundstation daugtherboard
2026-02-11 add Antenna desing for the desgin overview
2026-02-11 update motherboard
2026-02-12 include electronics photograph
2026-02-18 change gitignore settings
2026-02-18 include input from ignition system
2026-02-18 Add COM controller, commands UI, and sim v2
    Introduce a new telemetry serial controller and UI command window, plus a v2 Arduino simulation sketch and dependency updates.
    Added groundstation/gui/telemetry/com_controller.py which replaces the older telemetry_receiver, providing parsing, CSV/TXT logging, UI callbacks, thread-based listening, and a send_command API with 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
    Added CommandsWindow and integrated it into the UI (ui_manager) and com_monitor_controller now uses the new TelemetryReceiver (start/stop, set_ui_callback) and exposes controller for the commands UI.
    Updated ComMonitor table formatting and improved UI layout/titles.
    Added a richer arduino_simulation_sketch_
2026-02-21 place some components
2026-02-22 improve pcb layout
2026-02-25 Daughterboard PCB design worked on
2026-02-25 change dim to 40x70
2026-02-27 finalized design of daughterbaord
2026-02-27 add motherboard pcb
2026-02-28 add power traces to motherboard pcb
2026-03-01 update groundstation antenna design info
    included high res images and table for geometric parameters. Improved structure of the antenna section
2026-03-01 add helix mechanical design
    fixes #22
2026-03-01 update RF trace width
2026-03-04 add power supply via USB to Motherboard
2026-03-07 add purchase links to components
2026-03-08 finishing touches to motherboard
2026-03-15 add label to radio module leds
2026-03-19 generate files for MB
2026-03-19 Tidy up temp PCB files before merge
2026-03-20 fix file name typos
2026-03-21 inluce kicad custom libraries manual
    fixes #19
2026-03-22 include new pcb renderings
2026-03-28 update code for new groundstation pcb Fixes #33
2026-03-30 minor readme changes
2026-03-31 Remove FlightData simulation files
    Delete the FlightData simulation module and its example data
2026-04-11 Add helix antenna build manual and images
    Add a comprehensive Helix Antenna Build Manual (docs/antenna_assembly_manual.md) covering overview, bill of materials, step-by-step build phases, and a build checklist with references to 3D print fil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
    Include a full set of supporting photos files under docs/images/antenna_assembly to document pacifier prep, rod prep, epoxy application, coil winding, coil insertion, and final assembly.
    Fixes #16
2026-04-11 Organize media assets and update README paths
    Move media assets into structured directories (docs/, onboard/pcb/, groundstation/pcb/) and rename 3D model and image files accordingly.
    Update README.md to reference the new image locations and remove an unused image (media/images/meerkat_demo_1.png).
    These changes reorganize repository media for clearer project structure and maintain correct relative links in documentation.
    Fixes #41
    Causes #44
2026-04-11 Update antenna assembly mask image
2026-04-11 complete repo restructuring and fix linking issues
2026-04-12 update helix antenna assembly manual
    rework text, downsize images and more
2026-04-14 Fix minor issues
2026-04-15 reduce image size
2026-04-16 Use .venv for virtual environment in run.bat
    Update groundstation/gui/run.bat to create and activate the virtual environment in a hidden .venv directory instead of venv.
    The script now runs "%PYTHON_CMD% -m venv .venv" and activates via "call .venv\Scripts\activate".
    Functionality remains the same aside from using a .venv folder.
2026-04-25 include radiocrafts in library name
2026-04-25 include new improved renderin
2026-04-26 improve gitignore scope
2026-05-07 fix 3D Models and rearrange wires. Fixes #46
2026-05-07 rework README
    fixes #40
2026-05-08 add onboard and groundstation tocs
2026-05-09 improve readme structure and quicklinks
2026-05-15 Update Motherboard Pin Initialisations
2026-05-20 small update
    advances with #17 and #18
2026-05-26 Update helix_antenna_assembly_manual.md with centered pictures
2026-05-27 include new electronics design in design overview
    including onboard, MB and DB. fixes #17 fixes #18
2026-05-28 add soldering images to helix assembly manual
2026-05-31 Docs: Add groundstation GUI and architecture in design_overview.md
    Expand the GUI section in docs/design_overview.md
2026-05-31 fill functions for i2c connectivity
2026-06-02 Revise CHANGELOG format and add new entries
    Updated the CHANGELOG format and added new entries for unreleased features and changes.
2026-06-02 Restructure antenna folder: split into helical/ and add patch antenna
    groundstation/antenna/ now holds one subfolder per antenna design:
    - helical/: the existing 869 MHz helical antenna (moved unchanged)
    - patch/: new RHCP patch antenna simulation source imported from the
    standalone PatchAntennaSimulation project (source only: config.py,
    run.py, requirements.txt, src/*.py), with a scoped .gitignore for the
    regenerable openEMS/FDTD run output.
2026-06-03 Refactor patch antenna optimizer: share metrics, remove dead code, fix logic
    Structural cleanup (no change to simulation physics or exported PCB geometry):
    - Extract shared S11 / axial-ratio / centroid / eval-grid / failure-result
    helpers into new src/metrics.py, used by both the optimizer worker and the
    post-processor (removes copy-pasted numeric logic across three files).
    - Delete the dead _run_single method and its now-unused shutil/tempfile imports.
    - Drop the never-enabled _dbg tracer from build_sim.
2026-06-03 Patch antenna: fail fast on missing openEMS bindings + setup docs
    The CSXCAD/openEMS Python bindings are not on PyPI or conda, so a fresh
    clone dies with a deep "ModuleNotFoundError: No module named 'CSXCAD'"
    traceback. Add a guardrail tier so launches fail with clear guidance:
    - run.py: preflight_check() called first in main(). Self-heals the
    Windows DLL path (auto-sets OPENEMS_INSTALL_PATH to a standard openEMS
    install if unset), then verifies the bindings import; on failure prints
2026-06-03 @ Patch antenna: gitignore Claude Code session artifacts (.claude/) @
2026-06-03 update linkbudget calculation and simulation
    new 869 and 169 systems. new values for calculations chosen. fixes #24
2026-06-05 fix sending functions
    advances #54
2026-06-05 small changes
2026-06-05 Fix formatting
2026-06-05 Add radioModuleConfigure, commandReceive
    Add radioModuleSetup, radioModuleConfigure
    Add commandReceive
2026-06-06 rework radio module library
    include serial functions and rework function and attribute naming. fixes #54
2026-06-07 Patch antenna: KiCad export, footprints & assets
    Gerber-ready KiCad PCB export with soldermask openings and readable datasheet-style silk: front boresight farfield panel, back elevation panel and corner decoration. Includes the Wuerth end-launch SM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
2026-06-07 Patch antenna: test & tool suite
    Staged validation tests (single-feed, branch-line coupler, dual-feed, optimizer) plus inspection tools (build inspect, coupler circuit, geometry view) and the board-size sweep, on a shared bootstrap.
2026-06-07 Patch antenna: NF2FF efficiency / realised-gain rework + directivity units fix
    Implement the parked efficiency analysis, and fix two validated issues it exposed.
    Findings (dipole-calibrated, power-balance closes to 100%):
    - Directivity units bug: openEMS nf2ff.Dmax is a LINEAR ratio, not dBi. Reporting it
    raw under-read directivity by 10*log10 -- true boresight is 5.9 dBi, not 3.9.
    - Radiation efficiency is real, not an NF2FF artefact: the patch radiates only ~3% of
    accepted power (realised gain ~-9.6 dBic). A 150k iso-resistor probe decomposition
2026-06-08 Patch antenna: recentre W optimiser grid on measured resonance + retire dual-feed BOM/plan
    Pre-optimise review of the single-feed pipeline (geometry/code/design):
    - Optimiser W grid was symmetric about the seed (0.98/1.00/1.02), but the 150k
    confirmation run measured the W=82.5 seed at 875.4 MHz (+5.9 high). Resonance
    must come DOWN, i.e. W must grow; the AR null tracks resonance, so the symmetric
    grid would just reproduce AR ~4.8 dB at f_target. Recentre GRID_W_FRAC to
    (1.0000, 1.0067, 1.0133) so the predicted on-resonance W (x 875.4/869.525) sits
2026-06-08 Patch antenna: harden AR-null optimiser per adversarial review
    Adversarial multi-agent review of the AR-null fix confirmed one bug and surfaced cheap
    consistency hardening (the verified-not-real findings are addressed too as they are low-risk):
    - optimizer: per-phase hang guard now scales with the actual per-host work
    (max(PHASE_TIMEOUT_S, 4x waves x per-sim)), not a fixed 3 h calibrated to the 20-thread
    reference host - a slow/few-core box running 3 serial 150k waves was wrongly marked a
    timeout failure. [confirmed bug]
2026-06-08 Patch antenna: guard against empty NF2FF (zero far-field) in the optimiser worker
    The verification optimise exposed a resource limit: 9 concurrent sims at NrTS=150k returned
    EMPTY NF2FF (Prad~0, Dmax~0, AR=-inf) while the port S11 stayed valid - the openEMS NF2FF
    recording scales with NrTS and 9x150k apparently overran RAM/temp-disk (9x60k and 3x150k
    both worked). Those garbage sims returned ok=True with a finite cost (-1.20), which would
    silently pollute grid selection.
    The worker now validates res_f.Prad>0 and Dmax>0; otherwise it returns a failure_result
2026-06-08 Patch antenna: report realised cone-edge gain, de-stale link tool, add eps-robustness sweep + gates
    Post-adversarial-review honesty/correctness fixes (design unchanged; these correct how it is
    reported and add the missing pre-fab de-risk):
    - tests/tool_link_budget.py: was STALE (modelled the retired dual-feed at -9.6 dBic). Rewritten
    for the single-feed realised gains (+0.84 boresight, -2.0 cone-edge) and aligned to
    linkbudget.ipynb (G_TX -5, P_RX -114, L_TX+L_RX 6) so the two agree; margin tiers per the
    notebook. Closes the 10 dB floor across the helical 18.4 km (+19.6/+16.8 @10 km, +14.3/+11.5
2026-06-08 Patch antenna: fab release - remove front silk graph, add board + gerbers + front/back renders
2026-06-08 Patch antenna: centre top description on patch; move Patch/trunc labels to patch bottom-right; fix center-justify
2026-06-09 Patch antenna: qualify datasheet AR to band-robust + cone-worst values
2026-06-10 small typo in Packet.cpp with unint8_t
2026-06-10 Add led class and button class for the motherboard
2026-06-11 specify telemetry data packet structure
    advances #52
2026-06-11 include telemetry data encoding / decoding functions
2026-06-13 Update CP2102 LED setting manual
2026-06-13 Add new commands in operration cheat sheet
2026-06-29 remove images from radiocrafts datasheets
    replace with table
